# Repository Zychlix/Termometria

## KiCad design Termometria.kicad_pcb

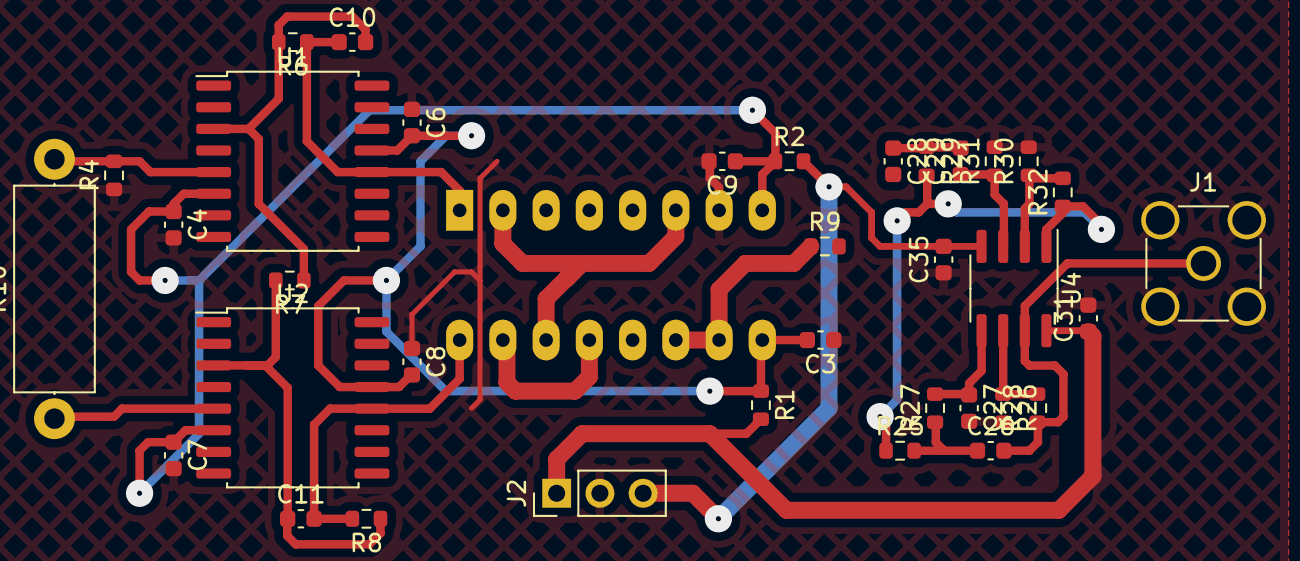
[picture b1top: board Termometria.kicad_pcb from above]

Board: 2 copper layers, 36 parts (1 on the bottom side), 23 nets.

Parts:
C3, C4, C6, C7, C8, C9: 1u 50V; C_0603_1608Metric
C10, C11: 10n; C_0603_1608Metric
C26, C27, C28, C29, C31, C35: C; C_0603_1608Metric
J1: Conn_Coaxial; SMA_Amphenol_901-144_Vertical
J2: Power; PinHeader_1x03_P2.54mm_Vertical
R1, R2, R9: 50; R_0603_1608Metric
R4: 100k; R_0603_1608Metric
R6, R8: 5.1k; R_0603_1608Metric
R7: 510; R_0603_1608Metric
R10: R; R_Axial_DIN0414_L11.9mm_D4.5mm_P15.24mm_Horizontal
R25, R26, R27, R28, R29, R30, R31, R32: R; R_0603_1608Metric
U1, U2: AD745; SOIC-16W_7.5x10.3mm_P1.27mm
U3: INA103; DIP-16_W7.62mm_LongPads
U4: NE5532; SOIC-8_3.9x4.9mm_P1.27mm

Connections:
+15V: C31.1, J2.1, R1.2, U4.8 (V+)
-15V: C35.2, J2.3, R2.2, U4.4 (V-)
/Amplifier Block/IN +: R4.2, R10.2, U1.5 (+)
/Amplifier Block/IN -: R10.1, U2.5 (+)
/Amplifier Block/OUT: C28.2, R9.2
GND: C3.1, C4.2, C6.1, C7.2, C8.1, C9.2, C27.2, C31.2, C35.1, J1.2 (Ext), J2.2, R4.1, R26.2, R30.2, R31.2, U3.7 (Ref)
unnamed: C26.1, R25.2, R27.1
unnamed: C28.1, C29.2, R29.1
unnamed: C26.2, J1.1 (In), R28.1, U4.7
unnamed: R25.1, R29.2, R32.1, U4.1
unnamed: C10.2, R6.2, R7.1, U1.3 (-)
unnamed: C11.1, R7.2, R8.1, U2.3 (-)
unnamed: C10.1, R6.1, U1.12, U3.1 (+)
unnamed: U3.2 (+G_Sense), U3.6 (+Rg), U3.14 (G=100)
unnamed: C11.2, R8.2, U2.12, U3.16 (-)
unnamed: U3.13 (-Rg), U3.15 (-G_Sense)
unnamed: R9.1, U3.10, U3.11 (Sense)
unnamed: C29.1, R31.1, U4.3 (+)
unnamed: R30.1, R32.2, U4.2 (-)
unnamed: C27.1, R27.2, U4.5 (+)
unnamed: R26.1, R28.2, U4.6 (-)
V+: C3.2, C6.2, C8.2, R1.1, U1.13 (V+), U2.13 (V+), U3.9 (V+)
V-: C4.1, C7.1, C9.1, R2.1, U1.6 (V-), U2.6 (V-), U3.8 (V-)

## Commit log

2023-06-11 latest
2023-06-11 module created
2023-06-11 layout made
